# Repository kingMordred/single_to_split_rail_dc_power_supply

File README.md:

# Single_to_split_rail_dc_power_supply

PCB design using KiCad 10.0 for a single to split rail dc power supply, converting an input of +6V ~ +12V to a +5V rail or a +12V/-12V rail.

### Schematic overview

### Pcb overview

### Board 3D viewer

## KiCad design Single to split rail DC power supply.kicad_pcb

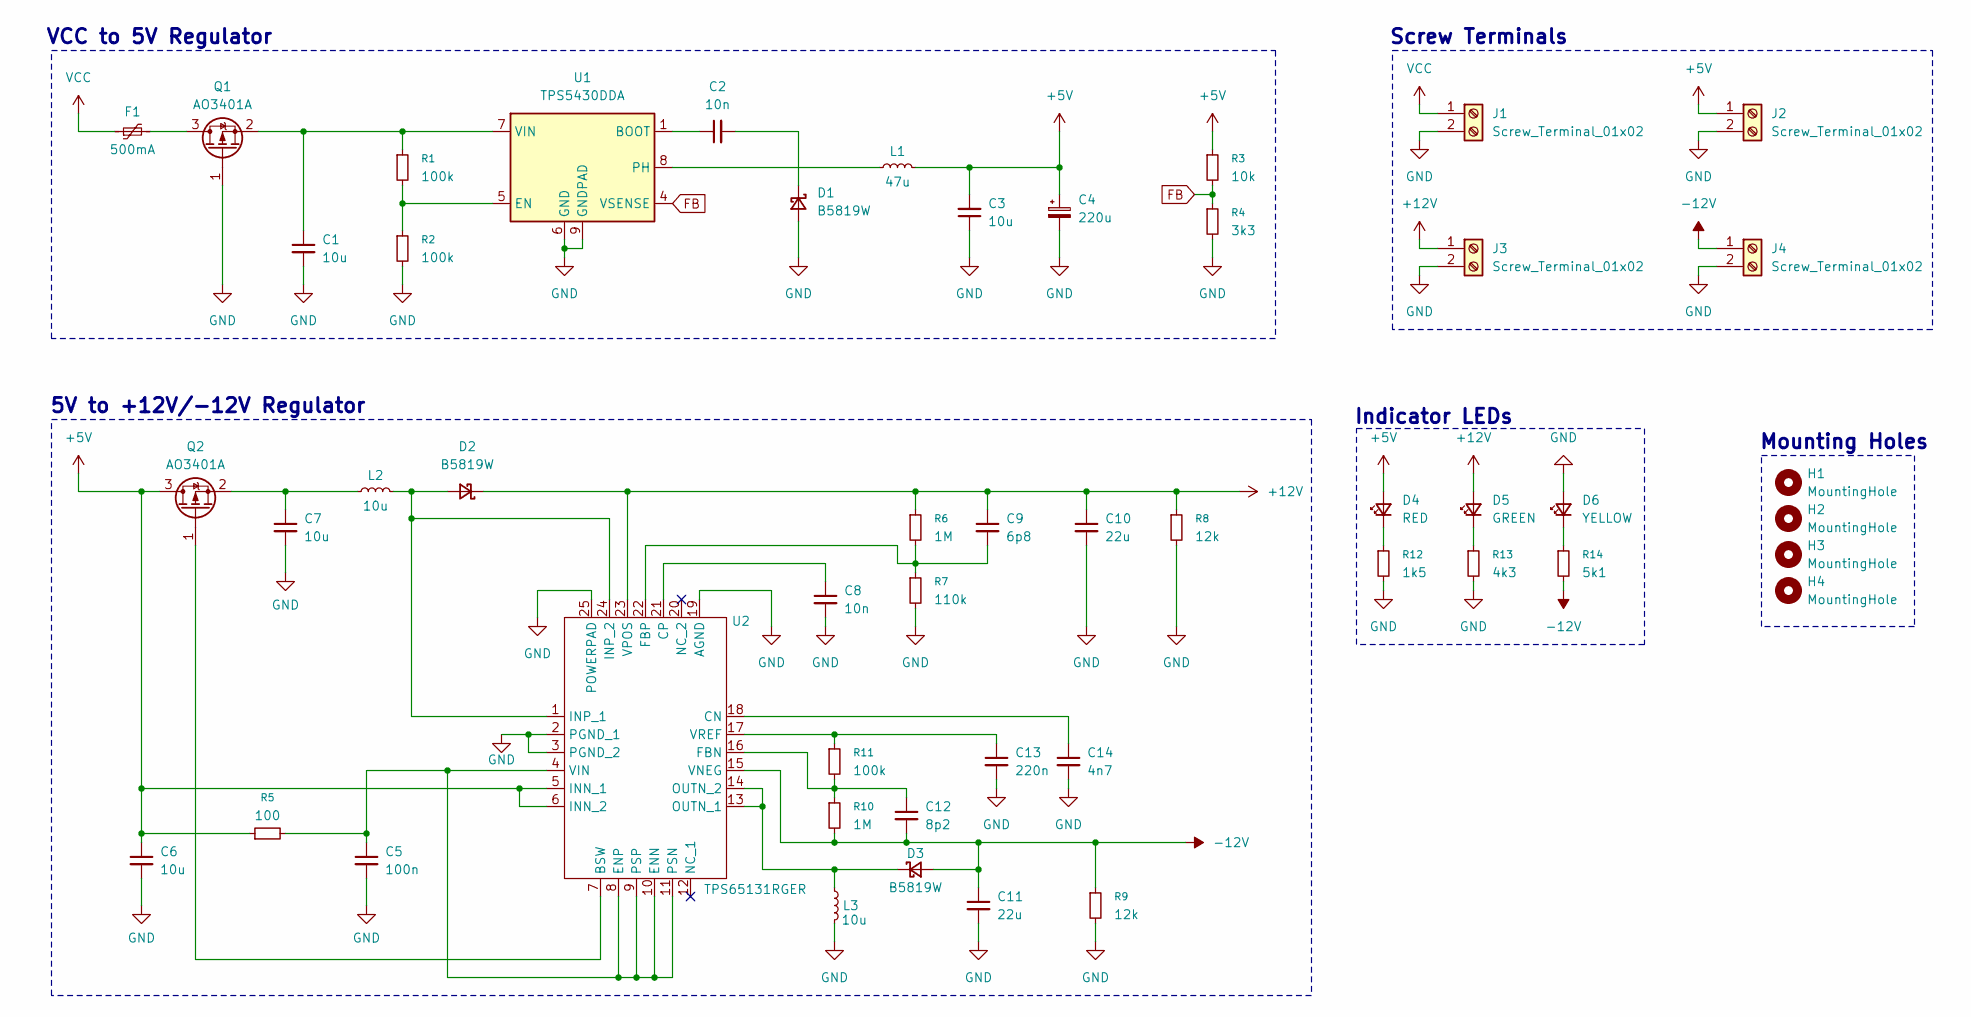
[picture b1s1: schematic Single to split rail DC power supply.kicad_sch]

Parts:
C1, C3, C6, C7: 10u; C_1206_3216Metric
C2, C8: 10n; C_0603_1608Metric
C4: 220u; CP_Elec_6.3x7.7
C5: 100n; C_0402_1005Metric
C9: 6p8; C_0402_1005Metric
C10, C11: 22u; C_1206_3216Metric
C12: 8p2; C_0402_1005Metric
C13: 220n; C_0603_1608Metric
C14: 4n7; C_0402_1005Metric
D1, D2, D3: B5819W; D_SOD-123
D4: RED; LED_0603_1608Metric
D5: GREEN; LED_0603_1608Metric
D6: YELLOW; LED_0603_1608Metric
F1: 500mA; Fuse_1206_3216Metric
H1, H2, H3, H4: MountingHole; MountingHole_4.3mm_M4_Pad_Via
J1, J2, J3, J4: Screw_Terminal_01x02; TerminalBlock_Phoenix_PT-1,5-2-5.0-H_1x02_P5.00mm_Horizontal
L1: 47u; L_1210_3225Metric
L2, L3: 10u; L_0603_1608Metric
Q1, Q2: AO3401A; SOT-23
R1, R2, R11: 100k; L_0603_1608Metric
R3: 10k; L_0603_1608Metric
R4: 3k3; L_0603_1608Metric
R5: 100; L_0603_1608Metric
R6, R10: 1M; L_1206_3216Metric
R7: 110k; L_0603_1608Metric
R8, R9: 12k; L_0603_1608Metric
R12: 1k5; L_0603_1608Metric
R13: 4k3; L_0603_1608Metric
R14: 5k1; L_0603_1608Metric
U1: TPS5430DDA; TI_SO-PowerPAD-8_ThermalVias
U2: TPS65131RGER; VQFN-24-1EP_4x4mm_P0.5mm_EP2.5x2.5mm

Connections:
+5V: C3.2, C4.1, C6.1, D4.2 (A), J2.1, L1.2, Q2.3 (D), R3.1, R5.1, U2.5 (INN_1), U2.6 (INN_2)
+12V: C9.1, C10.1, D2.1 (K), D5.2 (A), J3.1, R6.1, R8.1, U2.23 (VPOS)
-12V: C11.1, C12.2, D3.2 (A), J4.1, R9.1, R10.2, R14.2, U2.15 (VNEG)
FB: R3.2, R4.1, U1.4 (VSENSE)
GND: C1.2, C3.1, C4.2, C5.2, C6.2, C7.2, C8.2, C10.2, C11.2, C13.2, C14.2, D1.2 (A), D6.2 (A), J1.2, J2.2, J3.2, J4.2, L3.2, Q1.1 (G), R2.2, R4.2, R7.2, R8.2, R9.2, R12.2, R13.2, U1.6 (GND), U1.9 (GNDPAD), U2.2 (PGND_1), U2.3 (PGND_2), U2.19 (AGND), U2.25 (POWERPAD)
unnamed: C2.2, D1.1 (K)
unnamed: D2.2 (A), L2.2, U2.1 (INP_1), U2.24 (INP_2)
unnamed: D3.1 (K), L3.1, U2.13 (OUTN_1), U2.14 (OUTN_2)
unnamed: D4.1 (K), R12.1
unnamed: D5.1 (K), R13.1
unnamed: D6.1 (K), R14.1
unnamed: F1.2, Q1.3 (D)
unnamed: C1.1, Q1.2 (S), R1.1, U1.7 (VIN)
unnamed: Q2.1 (G), U2.7 (BSW)
unnamed: C7.1, L2.1, Q2.2 (S)
unnamed: C2.1, U1.1 (BOOT)
unnamed: R1.2, R2.1, U1.5 (EN)
unnamed: L1.1, U1.8 (PH)
unnamed: C14.1, U2.18 (CN)
unnamed: C8.1, U2.21 (CP)
unnamed: C5.1, R5.2, U2.4 (VIN), U2.8 (ENP), U2.9 (PSP), U2.10 (ENN), U2.11 (PSN)
unnamed: C12.1, R10.1, R11.2, U2.16 (FBN)
unnamed: C9.2, R6.2, R7.1, U2.22 (FBP)
unnamed: C13.1, R11.1, U2.17 (VREF)
VCC: F1.1, J1.1

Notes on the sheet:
Screw Terminals
Indicator LEDs
5V to +12V/-12V Regulator
Mounting Holes
VCC to 5V Regulator

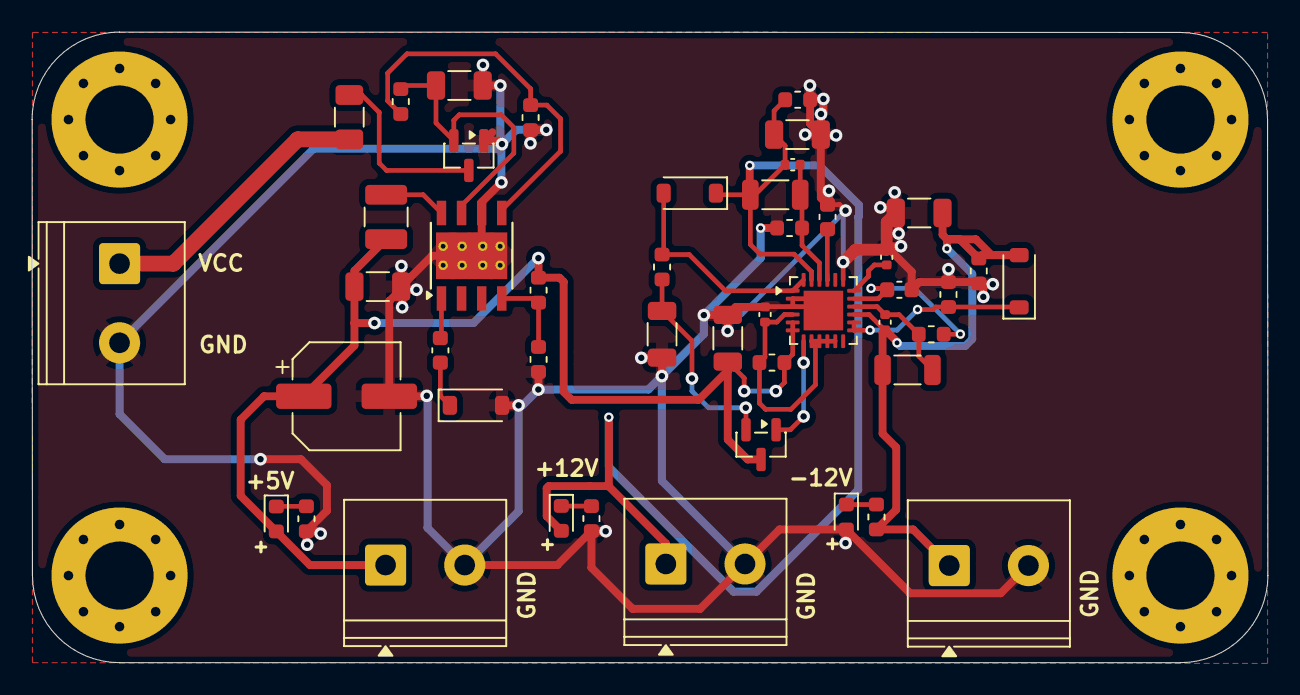
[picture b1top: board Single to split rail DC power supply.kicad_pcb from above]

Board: 2 copper layers, 78.0 x 39.8 mm, 50 parts (0 on the bottom side), 25 nets.
